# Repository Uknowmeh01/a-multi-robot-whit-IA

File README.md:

# AI Robot Rover 

A modular, 3D-printable indoor robot rover built around a Raspberry Pi 4 and an ESP32.

The project combines a parametric mechanical chassis, motor control, environmental sensors, a camera, autonomous behaviors, and a local web interface for controlling the robot from a phone or computer.

> [!IMPORTANT]
> The chassis design and software prototype are complete, but the full robot has not yet been physically assembled or tested.

## Project goals

The long-term goal is to build a small indoor assistant robot capable of:

- manual control from a phone;
- autonomous obstacle avoidance;
- camera-based object detection;
- navigation between rooms using visual markers;
- receiving simple voice commands;
- playing sounds or messages through a speaker;
- carrying small objects or messages around the house.

One planned example is telling the robot to go to the living room or to a family member's room. The robot would follow a known route, recognize a visual marker at its destination, stop, and play a notification sound.

## Hardware architecture

The robot uses two main computers:

### Raspberry Pi 4

The Raspberry Pi handles high-level functions:

- camera processing;
- object detection;
- web server and control interface;
- navigation logic;
- communication with the ESP32;
- future voice recognition and audio playback.

### ESP32

The ESP32 handles real-time hardware control:

- four DC motors;
- two TB6612FNG motor drivers;
- ultrasonic distance sensors;
- LEDs;
- environmental sensors;
- emergency stopping;
- serial communication with the Raspberry Pi.

## Planned hardware

- Raspberry Pi 4
- ESP32 development board
- 4 DC geared motors
- 2 TB6612FNG motor drivers
- Raspberry Pi Camera Module 3 Wide
- HC-SR04 ultrasonic sensors
- BH1750 light sensor
- microphone
- LEDs
- battery and power regulation system
- future USB speaker
- 3D-printed mechanical chassis
- M3 screws, nuts, and threaded inserts

Exact motor, battery, and mounting dimensions may still be adjusted to match the purchased hardware.

## Mechanical design

The chassis was designed as a parametric, multi-part KCL project in Zoo Design Studio.

### Main dimensions

| Property | Value |
|---|---:|
| Main deck size | 280 × 200 mm |
| Mechanical stack height | 148 mm |
| Approximate maximum length with angled inserts | 304 mm |
| M3 clearance hole | 3.4 mm |
| Maximum individual print area | 220 × 220 mm |

All individual parts are designed to fit on a standard 220 × 220 mm print bed.

### Mechanical features

- split lower deck for easier printing;
- three alignment tongues between lower-deck sections;
- aligned M3 joint holes;
- removable front and rear panels;
- removable corner brackets;
- reserved mounting areas for motors, battery, and motor drivers;
- cable-routing openings;
- separate sensor and camera inserts;
- modular upper electronics plate;
- removable top cover;
- editable shared parameters;
- exploded and inspection assemblies.

The current model intentionally contains only mechanical geometry and empty mounting provisions. Electronics, motors, wheels, batteries, cameras, sensors, and cables are not modeled as solid components.

## CAD files

The main CAD files include:

```text
cad/
├── main.kcl
├── explodedView.kcl
├── lowerDeckAssembly.kcl
├── parameters.kcl
├── chassisDimensions.md
├── removableCornerBracket.kcl
└── printable-parts/
```

The exact directory structure may differ depending on how the exported Zoo project is organized.

### Main CAD documents

- `main.kcl` contains the complete assembled chassis.
- `explodedView.kcl` contains the exploded assembly.
- `lowerDeckAssembly.kcl` provides a clear view of the split-deck joint.
- `parameters.kcl` contains shared editable dimensions.
- `chassisDimensions.md` documents dimensions, quantities, print envelopes, and export information.

### Printable parts

The project contains separate KCL parts for:

- front lower plate;
- rear lower plate;
- upper electronics plate;
- top cover;
- front sensor panel;
- rear utility panel;
- ultrasonic mounting insert;
- camera mounting insert;
- lower spacer posts;
- upper spacer posts;
- removable corner brackets.

STEP and STL binaries are not currently included because the original design environment exports KCL source files. Each printable part is isolated and ready to be exported from Zoo Design Studio.

## Software

The software is divided between the ESP32 and Raspberry Pi.

```text
software/
├── esp32/
└── raspberry-pi/
```

### ESP32 software

The ESP32 firmware is responsible for:

- motor control;
- serial command parsing;
- ultrasonic sensor measurements;
- lighting control;
- Bluetooth communication;
- autonomous safety behavior.

### Raspberry Pi software

The Raspberry Pi application includes:

- robot control logic;
- camera support;
- object-detection prototype;
- serial communication with the ESP32;
- operating-mode management;
- local web server;
- phone-friendly control interface;
- installation script;
- systemd service;
- tests.

## Web control interface

The Raspberry Pi hosts a local control website.

The interface is intended to provide:

- movement controls;
- speed adjustment;
- operating-mode selection;
- emergency stop;
- sensor information;
- connection status;
- AI detection information.

When the robot is connected to the same Wi-Fi network as a phone or computer, the interface can be opened using the Raspberry Pi's local IP address.

Example:

```text
http://192.168.1.42:5000
```

The exact IP address depends on the local network.

## Operating modes

The planned modes include:

### Manual mode

The user controls movement from the web interface or Bluetooth.

### Autonomous mode

The robot uses its distance sensors to move while avoiding obstacles.

### AI vision mode

The Raspberry Pi camera runs an object-detection prototype. The current software may use a person as its default target, but this behavior can be changed.

### Future navigation mode

A future version will use visual markers such as AprilTags or ArUco markers.

Each room or waypoint can have a unique marker. The robot will use these markers to follow routes and recognize when it has reached a destination.

## Current project status

### Completed

- [x] Parametric chassis design
- [x] Separate printable parts
- [x] Main mechanical assembly
- [x] Exploded assembly
- [x] Split lower-deck system
- [x] Removable corner brackets
- [x] Motor and battery reserved zones
- [x] ESP32 firmware prototype
- [x] Raspberry Pi software prototype
- [x] Local web interface prototype
- [x] Installation script and service files

### Not yet completed

- [ ] Print physical chassis parts
- [ ] Purchase and measure final hardware
- [ ] Assemble the complete rover
- [ ] Test motor direction and speed
- [ ] Test battery and power distribution
- [ ] Validate sensor measurements
- [ ] Validate emergency-stop behavior
- [ ] Test the Raspberry Pi and ESP32 protocol
- [ ] Test the web interface on the physical robot
- [ ] Add visual-marker navigation
- [ ] Add voice commands
- [ ] Add speaker notifications
- [ ] Document real-world test results

## Safety

Initial motor tests should be performed with the wheels raised off the ground.

Before autonomous testing:

- verify the emergency stop;
- use a low movement speed;
- keep cables away from wheels;
- securely mount the battery;
- add suitable power protection and a fuse;
- test in an open indoor area;
- keep the robot away from stairs and fragile objects.

## Repository structure

A possible repository layout is:

```text
AI-Robot-Rover/
├── README.md
├── LICENSE
├── .gitignore
├── docs/
│   └── images/
│       └── chassis-final.png
├── cad/
│   ├── main.kcl
│   ├── explodedView.kcl
│   ├── lowerDeckAssembly.kcl
│   ├── parameters.kcl
│   └── chassisDimensions.md
└── software/
    ├── esp32/
    └── raspberry-pi/
```

## Development notes

Some parts of the initial CAD and software were created with assistance from AI development tools.

All generated work will be reviewed, adapted, physically tested, and documented during the construction process. A generated design passing software validation does not guarantee that every mechanical tolerance or hardware integration detail will work correctly on the first physical build.

## Future ideas

- indoor room-to-room navigation;
- voice activation;
- destination markers;
- speaker announcements;
- automatic charging station;
- motor encoders;
- IMU-assisted movement;
- battery monitoring;
- removable payload platform;
- improved camera mount;
- physical emergency-stop button.

## License

A license has not yet been selected.

Before other people reuse the project, an open-source license such as the MIT License, Apache-2.0, or CERN Open Hardware Licence should be added.

## Author

Created by **Uknowmeh01** as a personal robotics and engineering project.

Built for learning, experimenting, and sharing with the Hack Club community.

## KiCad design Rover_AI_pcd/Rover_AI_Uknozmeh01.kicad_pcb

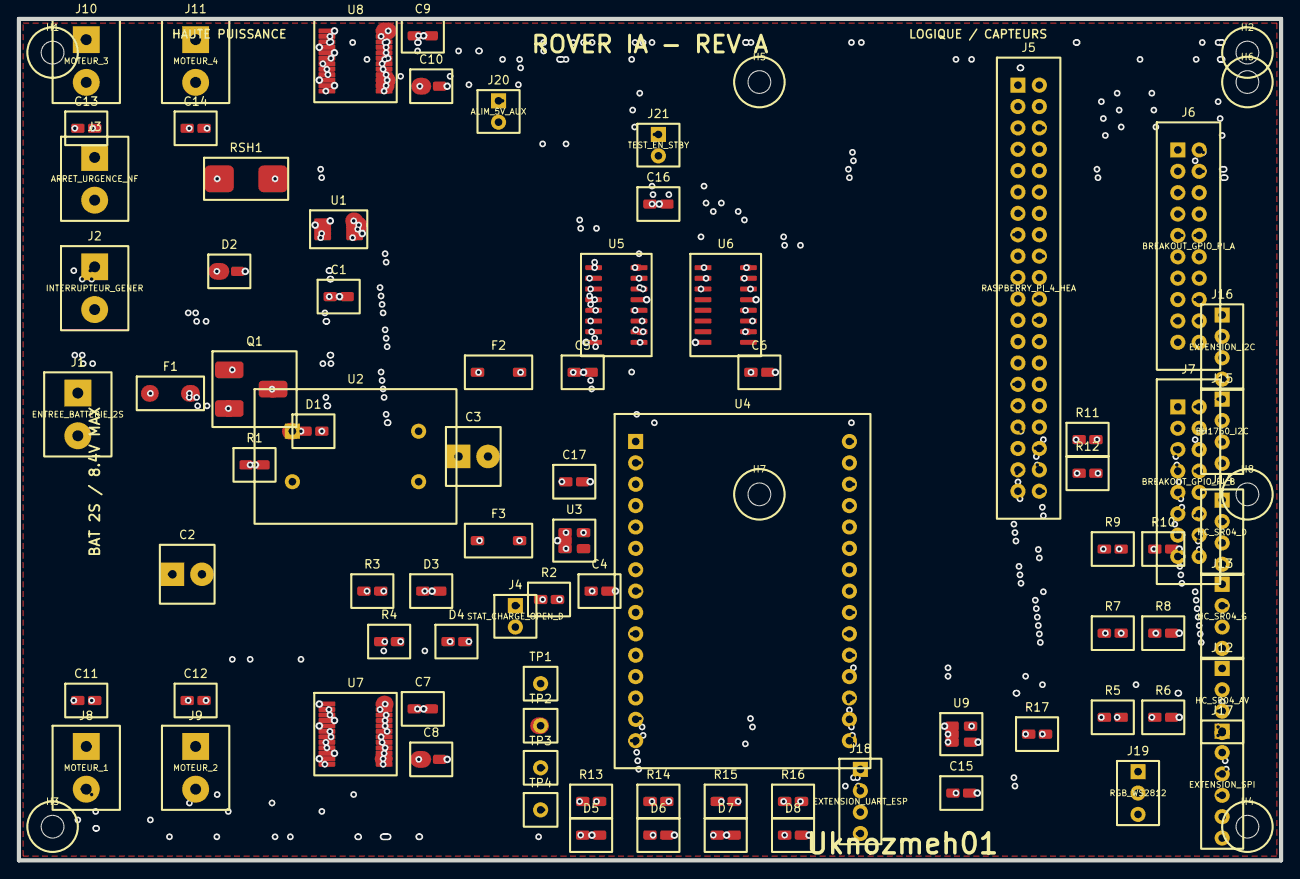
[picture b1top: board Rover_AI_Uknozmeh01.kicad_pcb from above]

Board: 4 copper layers, 150.0 x 100.0 mm, 89 parts (0 on the bottom side), 96 nets.

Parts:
C1, C5, C6, C7, C9, C15, C16: 100n; c
C2: 1000u_16V_lowESR; cap_big
C3: 470u_10V_lowESR; cap_big
C4: 1u; c
C8, C10: 10u_16V; c
C11, C12, C13, C14: 100n_MOTEUR; c
C17: 10u; c
D1: BZT52C10; d
D2: SMBJ9.0A; d
D3: LED_VERTE_POWER; led
D4: LED_ORANGE_CHARGE; led
D5: LED_BLEUE_ESP; led
D6: LED_VIOLETTE_AI; led
D7: LED_VERTE_AUTO; led
D8: LED_JAUNE_USER; led
F1: FUSIBLE_15A; fuse
F2: PTC_5A; fuse
F3: PTC_1.5A; fuse
H1, H2, H3, H4, H5, H6, H7, H8: MountingHole_2.7
J1: ENTREE_BATTERIE_2S; terminal2
J2: INTERRUPTEUR_GENERAL; terminal2
J3: ARRET_URGENCE_NF; terminal2
J4: STAT_CHARGE_OPEN_DRAIN; connector2
J5: RASPBERRY_PI_4_HEADER_40P; header2x20
J6: BREAKOUT_GPIO_PI_A; header2x10
J7: BREAKOUT_GPIO_PI_B; header2x8
J8: MOTEUR_1; terminal2
J9: MOTEUR_2; terminal2
J10: MOTEUR_3; terminal2
J11: MOTEUR_4; terminal2
J12: HC_SR04_AV; connector4
J13: HC_SR04_G; connector4
J14: HC_SR04_D; connector4
J15: BH1750_I2C; connector4
J16: EXTENSION_I2C; connector4
J17: EXTENSION_SPI; connector6
J18: EXTENSION_UART_ESP; connector4
J19: RGB_WS2812; connector3
J20: ALIM_5V_AUX; connector2
J21: TEST_EN_STBY; connector2
Q1: IPD90P03P4L-04; dpak
R1, R2: 100k; r
R3, R4, R13, R14, R15, R16: 1k; r
R5, R7, R9: 10k; r
R6, R8, R10: 20k; r
R11, R12: 4k7_DNP; r
R17: 330R; r
RSH1: 5mR_3W_1%; shunt
TP1: TP_GND; testpoint
TP2: TP_VMOTOR; testpoint
TP3: TP_5V; testpoint
TP4: TP_3V3; testpoint
U1: INA226AIDGSR; vssop10
U2: BUCK_5V_9A_D24V90F5; module4
U3: AP2112K-3.3; sot23_5
U4: ESP32_DEVKIT_V1_30P; module2x15
U5: 74HC595D_MOTEURS; soic16
U6: 74HC595D_LED; soic16
U7: TB6612FNG_M1_M2; ssop24
U8: TB6612FNG_M3_M4; ssop24
U9: SN74AHCT1G125; sot23_5

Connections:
+3V3: C1.1, C4.1, C5.1, C6.1, C7.1, C9.1, C16.1, J7.14, J15.1, J16.1, J17.1, J18.1, R11.1, R12.1, TP4.1, U1.6, U3.5, U4.30, U5.10, U5.16, U6.10, U6.16, U7.20, U8.20
+5V: C3.1, F2.1, F3.1, TP3.1, U2.3
+5V_LOGIC: C15.1, C17.1, F3.2, J7.15, J12.1, J13.1, J14.1, J19.1, J20.1, R2.2, R3.1, R4.1, U3.1, U4.15, U9.5
+5V_RPI: F2.2, J5.2, J5.4
CHG_LED_A: D4.1, R4.2
CHG_STAT: D4.2, J4.1
ECHO_AV: R5.2, R6.1, U4.2
ECHO_AV_5V: J12.3, R5.1
ECHO_D: R9.2, R10.1, U4.5
ECHO_D_5V: J14.3, R9.1
ECHO_G: R7.2, R8.1, U4.4
ECHO_G_5V: J13.3, R7.1
EN_3V3: R2.1, U3.3
ESP_RX0: J7.13, U4.19
ESP_TX0: J7.12, U4.18
GND: C1.2, C2.2, C3.2, C4.2, C5.2, C6.2, C7.2, C8.2, C9.2, C10.2, C15.2, C16.2, C17.2, D2.2, D3.2, D5.2, D6.2, D7.2, D8.2, J1.2, J4.2, J5.6, J5.9, J5.14, J5.20, J5.25, J5.30, J5.34, J5.39, J6.2, J6.20, J7.2, J7.16, J12.4, J13.4, J14.4, J15.2, J16.2, J17.2, J18.2, J19.3, J20.2, J21.2, R1.2, R6.2, R8.2, R10.2, TP1.1, U1.1, U1.2, U1.7, U2.2, U2.4, U3.2, U4.14, U4.21, U5.8, U5.13, U6.8, U6.13, U7.1, U7.4, U7.5, U7.10, U7.11, U8.1, U8.4, U8.5, U8.10, U8.11, U9.1, U9.4
I2C_SCL: J15.3, J16.3, R11.2, U1.5, U4.17
I2C_SDA: J15.4, J16.4, R12.2, U1.4, U4.20
LED_AI_A: R14.1, U6.1
LED_AI_A_R: D6.1, R14.2
LED_AUTO_A: R15.1, U6.2
LED_AUTO_A_R: D7.1, R15.2
LED_ESP_A: R13.1, U6.15
LED_ESP_A_R: D5.1, R13.2
LED_USER_A: R16.1, U6.3
LED_USER_A_R: D8.1, R16.2
M1_IN1: U5.15, U7.21
M1_IN2: U5.1, U7.22
M1_O1: C11.1, J8.1, U7.2, U7.3
M1_O2: C11.2, J8.2, U7.6, U7.7
M1_PWM: U4.8, U7.23
M2_IN1: U5.2, U7.18
M2_IN2: U5.3, U7.17
M2_O1: C12.1, J9.1, U7.12, U7.13
M2_O2: C12.2, J9.2, U7.8, U7.9
M2_PWM: U4.9, U7.16
M3_IN1: U5.4, U8.21
M3_IN2: U5.5, U8.22
M3_O1: C13.1, J10.1, U8.2, U8.3
M3_O2: C13.2, J10.2, U8.6, U8.7
M3_PWM: U4.10, U8.23
M4_IN1: U5.6, U8.18
M4_IN2: U5.7, U8.17
M4_O1: C14.1, J11.1, U8.12, U8.13
M4_O2: C14.2, J11.2, U8.8, U8.9
M4_PWM: U4.11, U8.16
MOTOR_STBY: J21.1, U4.27, U7.19, U8.19
PI_GPIO2: J5.3, J6.3
PI_GPIO3: J5.5, J6.4
PI_GPIO4: J5.7, J6.5
PI_GPIO5: J5.29, J6.18
PI_GPIO6: J5.31, J6.19
PI_GPIO7: J5.26, J6.17
PI_GPIO8: J5.24, J6.16
PI_GPIO9: J5.21, J6.13
PI_GPIO10: J5.19, J6.12
PI_GPIO11: J5.23, J6.15
PI_GPIO12: J5.32, J7.3
PI_GPIO13: J5.33, J7.4
PI_GPIO16: J5.36, J7.6
PI_GPIO17: J5.11, J6.6
PI_GPIO18: J5.12, J6.7
PI_GPIO19: J5.35, J7.5
PI_GPIO20: J5.38, J7.8
PI_GPIO21: J5.40, J7.9
PI_GPIO22: J5.15, J6.9
PI_GPIO23: J5.16, J6.10
PI_GPIO24: J5.18, J6.11
PI_GPIO25: J5.22, J6.14
PI_GPIO26: J5.37, J7.7
PI_GPIO27: J5.13, J6.8
PI_ID_SC: J5.28, J7.11
PI_ID_SD: J5.27, J7.10
PWR_LED_K: D3.1, R3.2
Q_GATE: D1.1, Q1.1, R1.1
RGB_DATA_3V3: U4.28, U9.2
RGB_DATA_5V: R17.1, U9.3
RGB_DATA_OUT: J19.2, R17.2
RPI_3V3: J5.1, J5.17, J6.1, J7.1
SPI_CS: J17.6, U4.29
SPI_MISO: J17.5, U4.22
SR_CHAIN: U5.9, U6.14
SR_CLK: J17.3, U4.23, U5.11, U6.11
SR_DATA: J17.4, U4.16, U5.14
SR_LATCH: U4.24, U5.12, U6.12
TRIG_AV: J12.2, U4.6
TRIG_D: J14.2, U4.13
TRIG_G: J13.2, U4.7
UART_RX_ESP: J5.8, J18.4, U4.26
UART_TX_ESP: J5.10, J18.3, U4.25
VBAT_ESTOP: J3.2, RSH1.1, U1.10
VBAT_FUSED: F1.2, Q1.3
VBAT_PROTECTED: D1.2, J2.1, Q1.2
VBAT_RAW: F1.1, J1.1
VBAT_SW: J2.2, J3.1
VMOTOR: C2.1, C8.1, C10.1, D2.1, RSH1.2, TP2.1, U1.8, U1.9, U2.1, U7.14, U7.15, U7.24, U8.14, U8.15, U8.24

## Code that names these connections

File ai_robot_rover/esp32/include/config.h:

#pragma once

#include <Arduino.h>

namespace Config {

// IMPORTANT : valeurs de reference pour ESP32 DevKit V1. Verifier le cablage
// avant d'alimenter. Les ECHO HC-SR04 (5 V) exigent des diviseurs vers 3,3 V.
constexpr uint32_t SERIAL_BAUD = 115200;
constexpr char BLUETOOTH_NAME[] = "AI-Robot-Rover";

// Deux TB6612FNG. Relier physiquement les deux broches STBY ensemble.
constexpr uint8_t MOTOR_STBY_PIN = 4;
constexpr uint8_t FL_IN1_PIN = 13;
constexpr uint8_t FL_IN2_PIN = 14;
constexpr uint8_t FL_PWM_PIN = 25;
constexpr uint8_t RL_IN1_PIN = 26;
constexpr uint8_t RL_IN2_PIN = 27;
constexpr uint8_t RL_PWM_PIN = 33;
constexpr uint8_t FR_IN1_PIN = 16;
constexpr uint8_t FR_IN2_PIN = 17;
constexpr uint8_t FR_PWM_PIN = 18;
constexpr uint8_t RR_IN1_PIN = 19;
constexpr uint8_t RR_IN2_PIN = 23;
constexpr uint8_t RR_PWM_PIN = 5;

constexpr bool FL_INVERTED = false;
constexpr bool RL_INVERTED = false;
constexpr bool FR_INVERTED = true;
constexpr bool RR_INVERTED = true;

constexpr uint8_t PWM_CHANNEL_FL = 0;
constexpr uint8_t PWM_CHANNEL_RL = 1;
constexpr uint8_t PWM_CHANNEL_FR = 2;
constexpr uint8_t PWM_CHANNEL_RR = 3;
constexpr uint32_t PWM_FREQUENCY = 18000;
constexpr uint8_t PWM_RESOLUTION_BITS = 8;
constexpr uint8_t MAX_SPEED = 210;
constexpr uint8_t DEFAULT_SPEED = 130;
constexpr uint8_t MIN_TEST_SPEED = 55;
constexpr uint8_t AUTONOMOUS_SPEED = 125;
constexpr uint8_t TURN_SPEED = 115;
constexpr uint8_t REVERSE_SPEED = 95;
constexpr uint8_t ACCEL_STEP = 6;
constexpr uint8_t DECEL_STEP = 10;
constexpr uint32_t MOTOR_RAMP_INTERVAL_MS = 20;
constexpr uint32_t COMMAND_TIMEOUT_MS = 700;
constexpr uint32_t SERIAL_LINK_TIMEOUT_MS = 2500;
constexpr uint32_t BLUETOOTH_LINK_TIMEOUT_MS = 1200;

// GPIO 2, 12 et 15 sont des broches de strapping sur de nombreuses cartes.
// Les TRIG ne doivent jamais les tirer au niveau oppose pendant le demarrage.
constexpr uint8_t US_LEFT_TRIG_PIN = 2;
constexpr uint8_t US_LEFT_ECHO_PIN = 34;
constexpr uint8_t US_CENTER_TRIG_PIN = 15;
constexpr uint8_t US_CENTER_ECHO_PIN = 35;
constexpr uint8_t US_RIGHT_TRIG_PIN = 12;
constexpr uint8_t US_RIGHT_ECHO_PIN = 39;
constexpr uint32_t ULTRASONIC_TIMEOUT_US = 24000;
constexpr uint32_t ULTRASONIC_SENSOR_SPACING_MS = 35;
constexpr uint8_t ULTRASONIC_MEDIAN_SAMPLES = 5;
constexpr float ULTRASONIC_MIN_VALID_CM = 2.0F;
constexpr float ULTRASONIC_MAX_VALID_CM = 400.0F;
constexpr float SLOW_DISTANCE_CM = 55.0F;
constexpr float MIN_DISTANCE_CM = 28.0F;
constexpr float EMERGENCY_DISTANCE_CM = 12.0F;
constexpr uint8_t SENSOR_MAX_CONSECUTIVE_FAILURES = 8;

constexpr uint8_t I2C_SDA_PIN = 21;
constexpr uint8_t I2C_SCL_PIN = 22;
constexpr uint8_t BH1750_ADDRESS = 0x23;
constexpr uint32_t LIGHT_READ_INTERVAL_MS = 300;
constexpr float DARK_THRESHOLD_LUX = 35.0F;

constexpr uint8_t SOUND_ADC_PIN = 36;
constexpr uint16_t SOUND_STRONG_THRESHOLD = 2850;
constexpr float SOUND_FILTER_ALPHA = 0.12F;
constexpr uint32_t SOUND_SAMPLE_INTERVAL_MS = 5;
constexpr uint32_t CLAP_DEBOUNCE_MS = 900;

// Bande ou anneau WS2812 : plusieurs LEDs pilotees avec une seule broche.
constexpr uint8_t LED_DATA_PIN = 32;
constexpr uint16_t LED_COUNT = 4;
constexpr uint8_t LED_BRIGHTNESS = 60;
constexpr uint32_t LED_BLINK_INTERVAL_MS = 350;

constexpr uint32_t TELEMETRY_INTERVAL_MS = 250;
constexpr uint32_t STATUS_INTERVAL_MS = 1000;
constexpr uint32_t AUTONOMOUS_REVERSE_MS = 550;
constexpr uint32_t AUTONOMOUS_TURN_MS = 650;
constexpr uint32_t AUTONOMOUS_STUCK_TIMEOUT_MS = 7000;
constexpr uint8_t MAX_COMMAND_LENGTH = 96;

}  // namespace Config
